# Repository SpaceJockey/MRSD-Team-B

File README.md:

MRSD-Team-B
===========

The best team is sometimes the B team...

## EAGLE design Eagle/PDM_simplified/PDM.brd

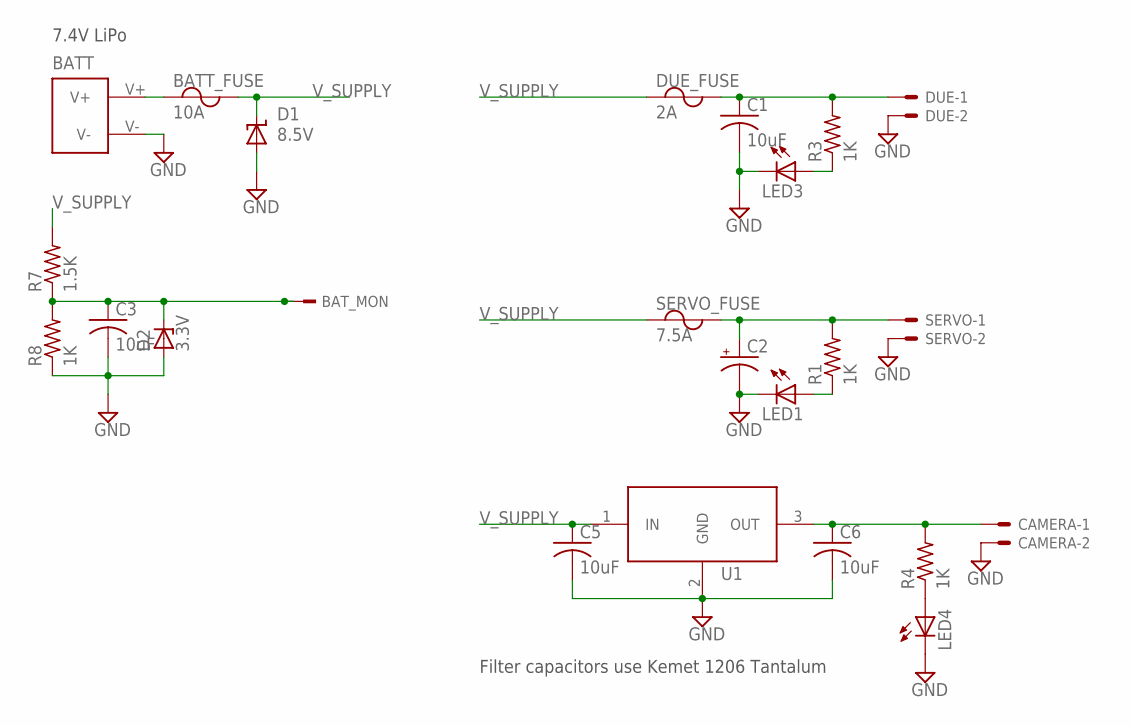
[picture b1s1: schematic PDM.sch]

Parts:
BATT: CON_XT60-; CON_XT60_PCB_MALE
BATT_FUSE: 10A; MINI_ATO
BAT_MON: TSW-101-02-S-S
C1, C3, C5, C6: 10uF; C1206K
C2: CPOL-USTT5D11; TT5D11
CAMERA: 5566-2
D1: 8.5V; SMBJ
D2: 3.3V; SOD80C
DUE: 5566-2
DUE_FUSE: 2A; MINI_ATO
LED1, LED3, LED4: LEDSML1206; SML1206
R1, R3, R4, R8: 1K; R1206
R7: 1.5K; R1206
SERVO: 5566-2
SERVO_FUSE: 7.5A; MINI_ATO
U1: MIC29150/29300/29500VERTICAL; TO220V

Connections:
GND: BATT.V-, C1.2, C2.-, C3.2, C5.2, C6.2, CAMERA.2, D1.A, D2.A, DUE.2, LED1.C, LED3.C, LED4.C, R8.1, SERVO.2, U1.2 (GND)
unnamed: BATT.V+, BATT_FUSE.P$2 (1)
unnamed: C1.1, DUE.1, DUE_FUSE.P$3 (2), R3.2
unnamed: LED1.A, R1.1
unnamed: C6.1, CAMERA.1, R4.2, U1.3 (OUT)
unnamed: LED3.A, R3.1
unnamed: LED4.A, R4.1
unnamed: C2.+, R1.2, SERVO.1, SERVO_FUSE.P$3 (2)
unnamed: BAT_MON.1, C3.1, D2.C, R7.1, R8.2
V_SUPPLY: BATT_FUSE.P$3 (2), C5.1, D1.C, DUE_FUSE.P$2 (1), R7.2, SERVO_FUSE.P$2 (1), U1.1 (IN)

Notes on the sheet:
Filter capacitors use Kemet 1206 Tantalum
7.4V LiPo

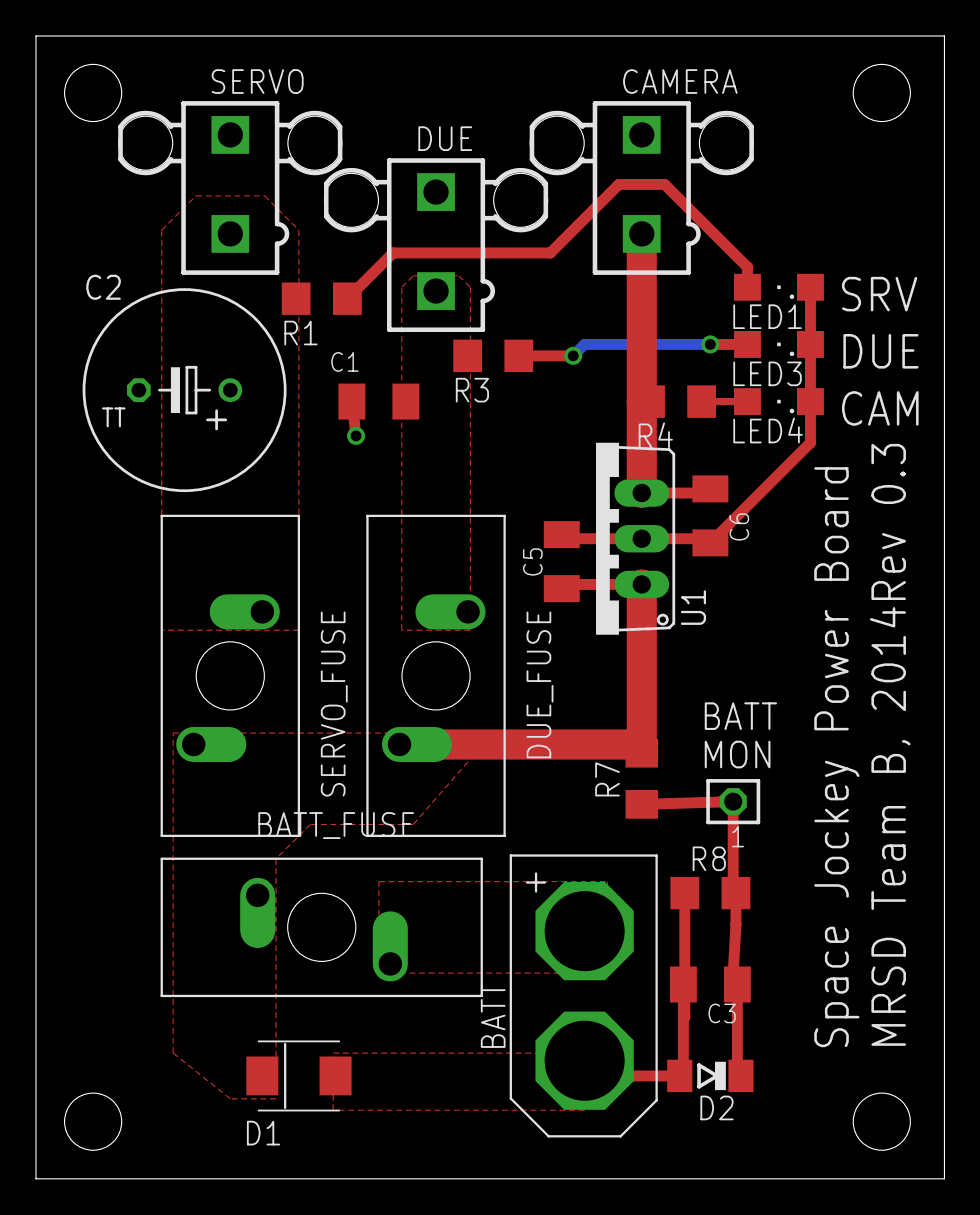
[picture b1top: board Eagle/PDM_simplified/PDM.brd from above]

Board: 2 copper layers, 50.5 x 63.5 mm, 24 parts (0 on the bottom side), 10 nets.

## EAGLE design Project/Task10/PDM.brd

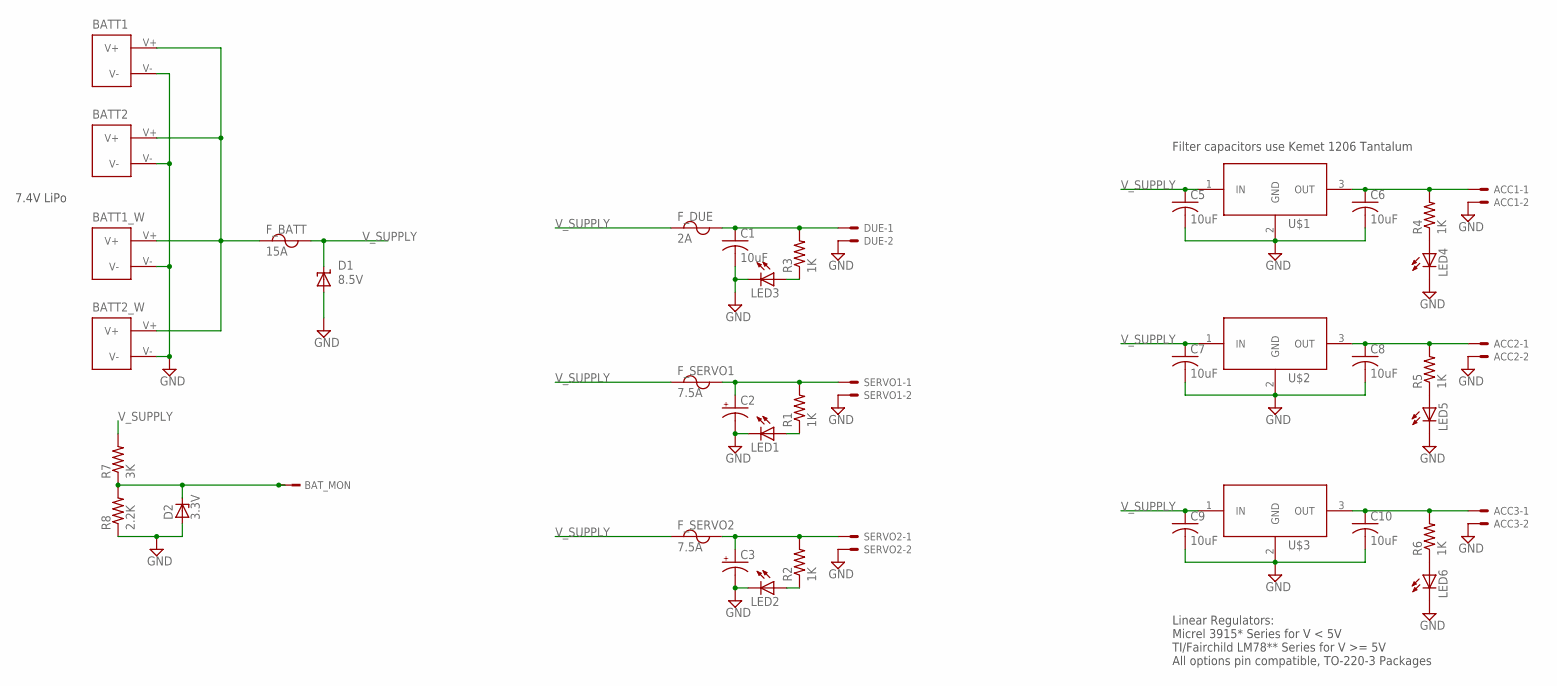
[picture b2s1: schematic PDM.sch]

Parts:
ACC1, ACC2, ACC3: 5566-2
BATT1, BATT2: CON_XT60-PCB_MOUNT; CON_XT60_PCB_MOUNT
BATT1_W, BATT2_W: CON_XT60-PIGTAIL; CON_XT60_PIGTAIL
BAT_MON: TSW-101-02-S-S
C1, C5, C6, C7, C8, C9, C10: 10uF; C1206K
C2, C3: CPOL-USTT5D11; TT5D11
D1: 8.5V; SMBJ
D2: 3.3V; SMB
DUE: 5566-2
F_BATT: 15A; ATO
F_DUE: 2A; ATO
F_SERVO1, F_SERVO2: 7.5A; ATO
LED1, LED2, LED3, LED4, LED5, LED6: LEDSML1206; SML1206
R1, R2, R3, R4, R5, R6: 1K; R1206
R7: 3K; R1206
R8: 2.2K; R1206
SERVO1, SERVO2: 5566-2
U$1, U$2, U$3: MIC29150/29300/29500VERTICAL; TO220V

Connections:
GND: ACC1.2, ACC2.2, ACC3.2, BATT1.V-, BATT1_W.V-, BATT2.V-, BATT2_W.V-, C1.2, C2.-, C3.-, C5.2, C6.2, C7.2, C8.2, C9.2, C10.2, D1.A, D2.A, DUE.2, LED1.C, LED2.C, LED3.C, LED4.C, LED5.C, LED6.C, R8.1, SERVO1.2, SERVO2.2, U$1.2 (GND), U$2.2 (GND), U$3.2 (GND)
unnamed: C3.+, F_SERVO2.B1 (2), F_SERVO2.B2 (2), F_SERVO2.B3 (2), F_SERVO2.B4 (2), R2.2, SERVO2.1
unnamed: BATT1.V+, BATT1_W.V+, BATT2.V+, BATT2_W.V+, F_BATT.A1 (1), F_BATT.A2 (1), F_BATT.A3 (1), F_BATT.A4 (1)
unnamed: C1.1, DUE.1, F_DUE.B1 (2), F_DUE.B2 (2), F_DUE.B3 (2), F_DUE.B4 (2), R3.2
unnamed: LED1.A, R1.1
unnamed: ACC1.1, C6.1, R4.2, U$1.3 (OUT)
unnamed: LED2.A, R2.1
unnamed: ACC2.1, C8.1, R5.2, U$2.3 (OUT)
unnamed: LED3.A, R3.1
unnamed: LED4.A, R4.1
unnamed: C2.+, F_SERVO1.B1 (2), F_SERVO1.B2 (2), F_SERVO1.B3 (2), F_SERVO1.B4 (2), R1.2, SERVO1.1
unnamed: LED5.A, R5.1
unnamed: BAT_MON.1, D2.C, R7.1, R8.2
unnamed: ACC3.1, C10.1, R6.2, U$3.3 (OUT)
unnamed: LED6.A, R6.1
V_SUPPLY: C5.1, C7.1, C9.1, D1.C, F_BATT.B1 (2), F_BATT.B2 (2), F_BATT.B3 (2), F_BATT.B4 (2), F_DUE.A1 (1), F_DUE.A2 (1), F_DUE.A3 (1), F_DUE.A4 (1), F_SERVO1.A1 (1), F_SERVO1.A2 (1), F_SERVO1.A3 (1), F_SERVO1.A4 (1), F_SERVO2.A1 (1), F_SERVO2.A2 (1), F_SERVO2.A3 (1), F_SERVO2.A4 (1), R7.2, U$1.1 (IN), U$2.1 (IN), U$3.1 (IN)

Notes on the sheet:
Linear Regulators: Micrel 3915* Series for V < 5V TI/Fairchild LM78** Series for V >= 5V All options pin compatible, TO-220-3 Packages
Filter capacitors use Kemet 1206 Tantalum
7.4V LiPo

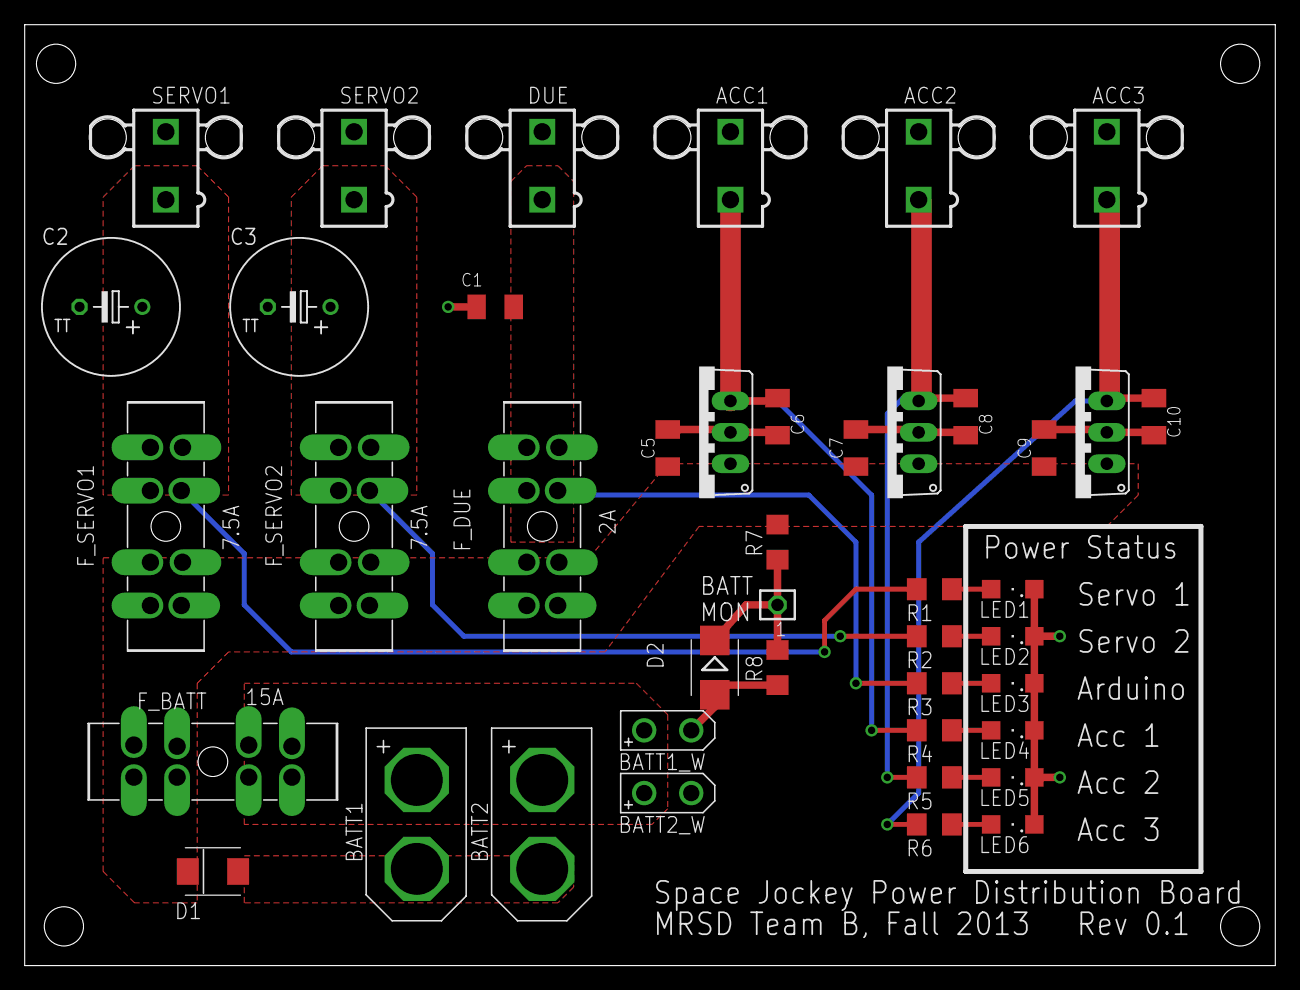
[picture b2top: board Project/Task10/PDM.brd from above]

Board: 2 copper layers, 101.3 x 76.2 mm, 43 parts (0 on the bottom side), 16 nets.

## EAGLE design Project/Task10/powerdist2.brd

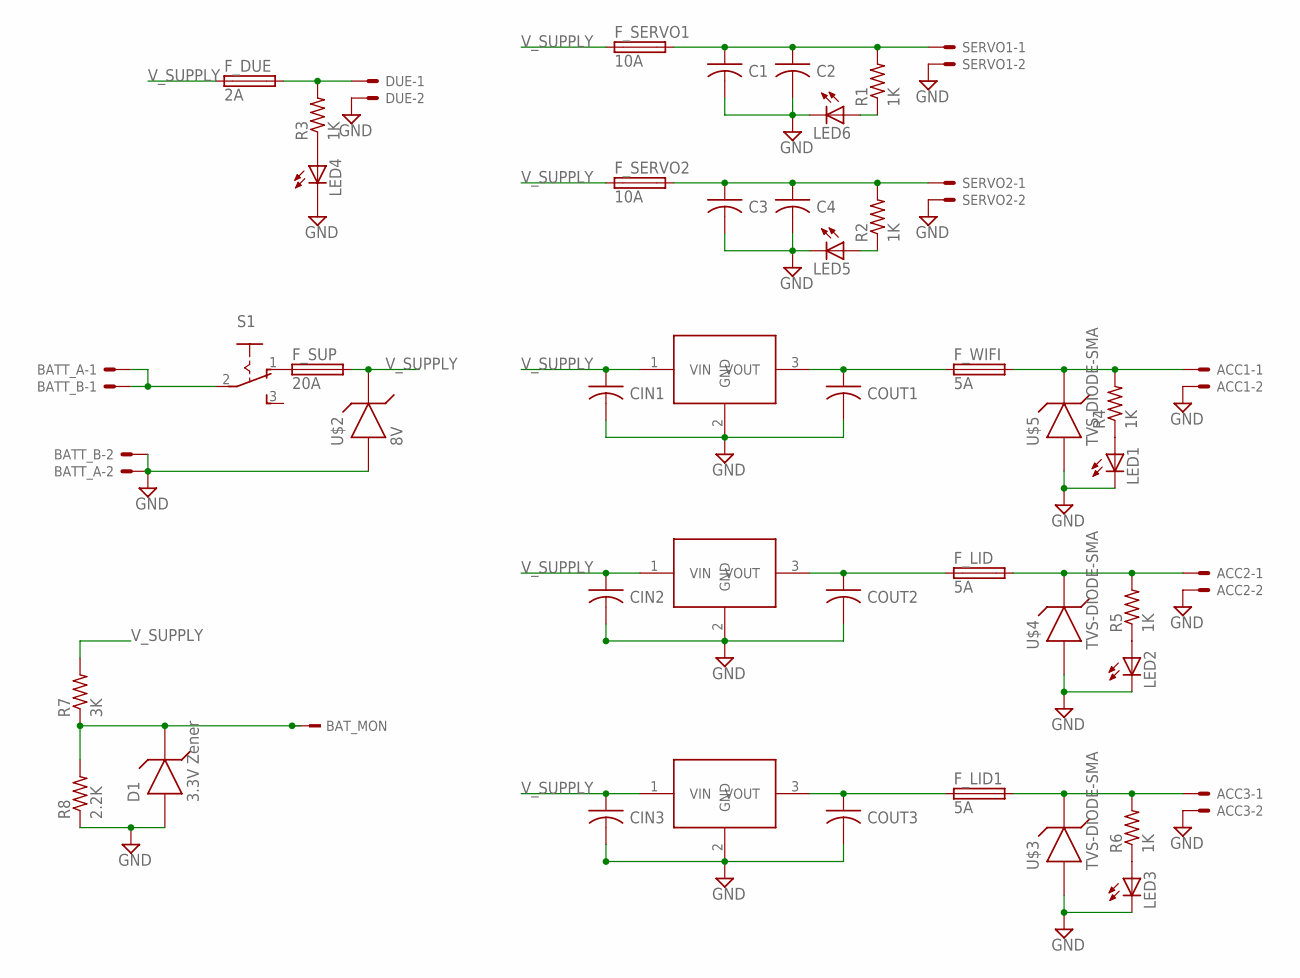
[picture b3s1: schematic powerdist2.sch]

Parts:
ACC1: C-GRID-02-70553; 70553-02
ACC2, ACC3: 5566-2
BATT_A: 22-23-2021
BATT_B: 22-23-2021
BAT_MON: TSW-101-02-S-S
C1, C2, C3, C4: CAPACITORTH_CAP; C025-025X050
CIN1, CIN2, CIN3: CAPACITORTH_CAP; C025-025X050
COUT1, COUT2, COUT3: CAPACITORTH_CAP; C025-025X050
D1: 3.3V Zener; SMA
DUE: C-GRID-02-70553; 70553-02
F_DUE: 2A; GSH15
F_LID, F_LID1: 5A; GSH15
F_SERVO1, F_SERVO2: 10A; GSH15
F_SUP: 20A; GSH15
F_WIFI: 5A; GSH15
LED1, LED2, LED3, LED4, LED5, LED6: LEDCHIP-LED0805; CHIP-LED0805
R1, R2, R3, R4, R5, R6: 1K; 0309/10
R7: 3K; 0309/10
R8: 2.2K; 0309/10
S1: 255SB
SERVO1, SERVO2: 5566-2
U$1, U$6, U$7: MIC29150/29300/29500; TO220
U$2: 8V; SMA
U$3, U$4, U$5: TVS-DIODE-SMA; SMA

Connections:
GND: ACC1.2, ACC2.2, ACC3.2, BATT_A.2, BATT_B.2, C1.2, C2.2, C3.2, C4.2, CIN1.2, CIN2.2, CIN3.2, COUT1.2, COUT2.2, COUT3.2, D1.AN, DUE.2, LED1.C, LED2.C, LED3.C, LED4.C, LED5.C, LED6.C, R8.1, SERVO1.2, SERVO2.2, U$1.2 (GND), U$2.AN, U$3.AN, U$4.AN, U$5.AN, U$6.2 (GND), U$7.2 (GND)
unnamed: C3.1, C4.1, F_SERVO2.2, R2.2, SERVO2.1
unnamed: ACC2.1, F_LID.2, R5.2, U$4.CAT
unnamed: DUE.1, F_DUE.2, R3.2
unnamed: LED6.A, R1.1
unnamed: COUT1.1, F_WIFI.1, U$7.3 (VOUT)
unnamed: ACC1.1, F_WIFI.2, R4.2, U$5.CAT
unnamed: LED5.A, R2.1
unnamed: COUT2.1, F_LID.1, U$6.3 (VOUT)
unnamed: BATT_A.1, BATT_B.1, S1.2
unnamed: LED4.A, R3.1
unnamed: LED1.A, R4.1
unnamed: F_SUP.1, S1.1 (O)
unnamed: C1.1, C2.1, F_SERVO1.2, R1.2, SERVO1.1
unnamed: LED2.A, R5.1
unnamed: BAT_MON.1, D1.CAT, R7.1, R8.2
unnamed: COUT3.1, F_LID1.1, U$1.3 (VOUT)
unnamed: ACC3.1, F_LID1.2, R6.2, U$3.CAT
unnamed: LED3.A, R6.1
V_SUPPLY: CIN1.1, CIN2.1, CIN3.1, F_DUE.1, F_SERVO1.1, F_SERVO2.1, F_SUP.2, R7.2, U$1.1 (VIN), U$2.CAT, U$6.1 (VIN), U$7.1 (VIN)

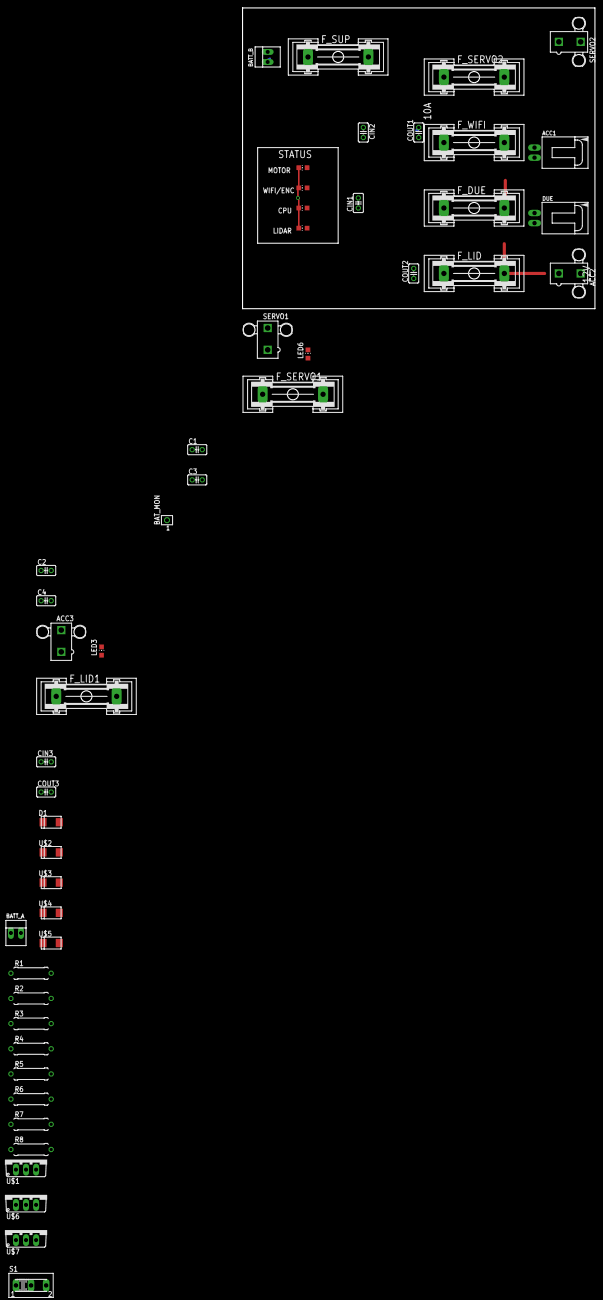
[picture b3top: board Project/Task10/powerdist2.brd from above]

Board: 2 copper layers, 88.9 x 75.9 mm, 49 parts (0 on the bottom side), 20 nets.

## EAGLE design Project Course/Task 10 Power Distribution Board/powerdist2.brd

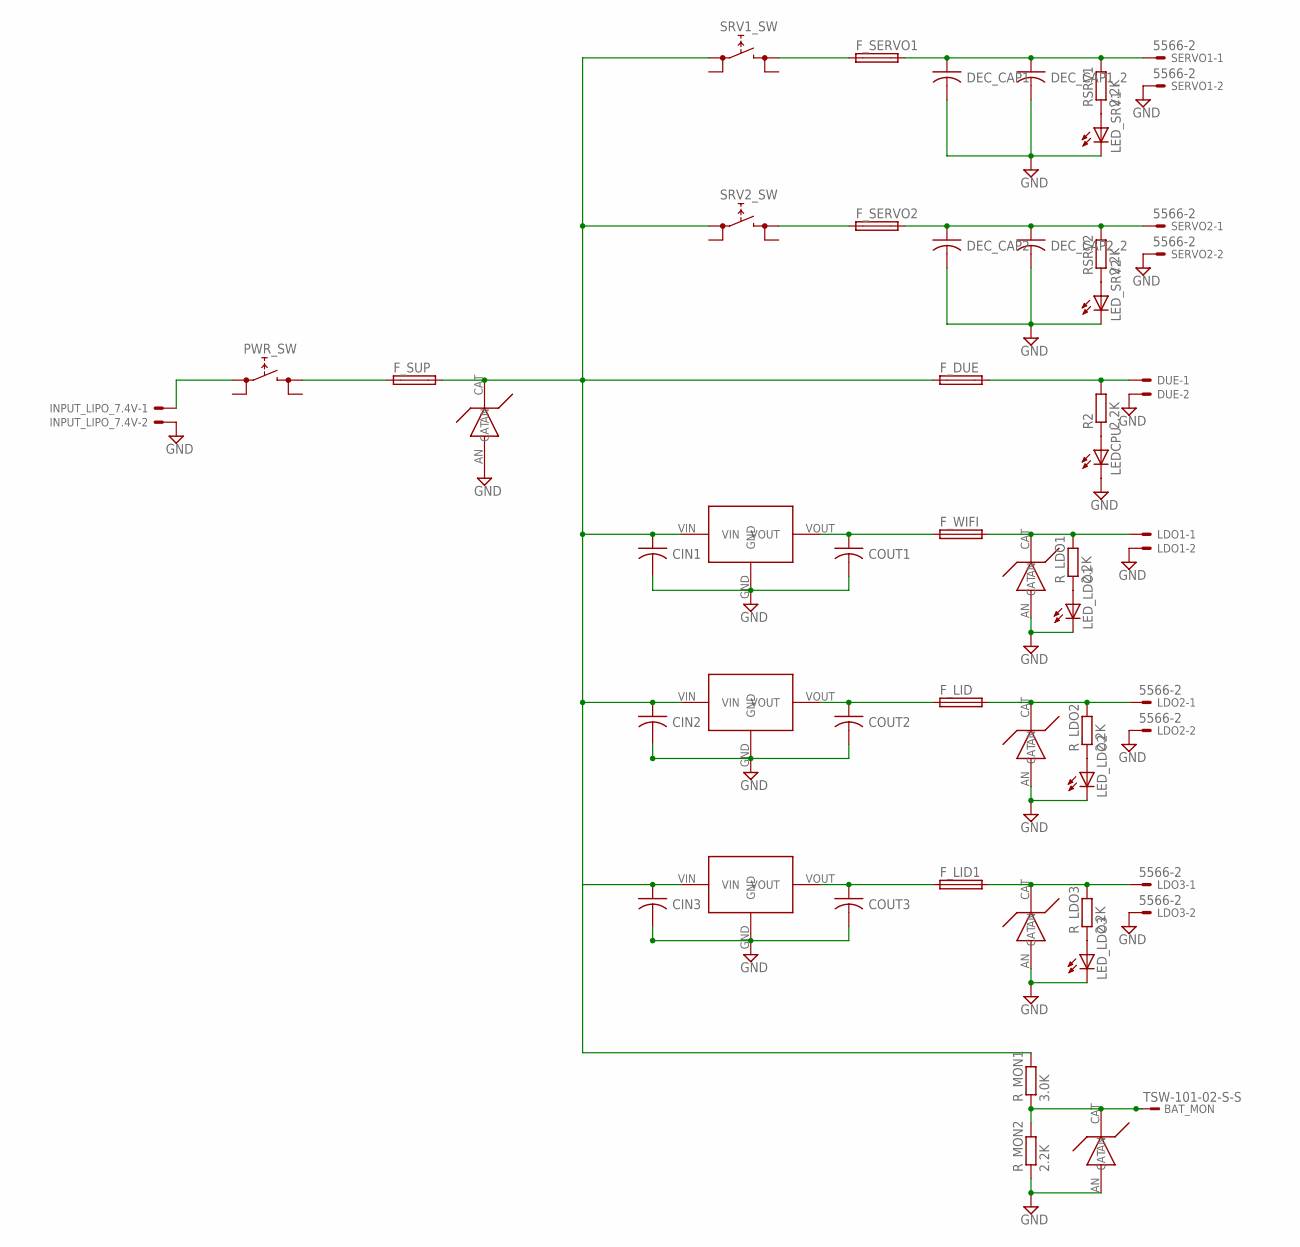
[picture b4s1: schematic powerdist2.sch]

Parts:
BAT_MON: TSW-101-02-S-S
CIN1, CIN2, CIN3: CAPACITORTH_CAP; C025-025X050
COUT1, COUT2, COUT3: CAPACITORTH_CAP; C025-025X050
DEC_CAP1, DEC_CAP1_2, DEC_CAP2, DEC_CAP2_2: CAPACITORTH_CAP; C025-025X050
DUE: C-GRID-02-70553; 70553-02
F_DUE: GSH15
F_LID, F_LID1: GSH15
F_SERVO1, F_SERVO2: GSH15
F_SUP: GSH15
F_WIFI: GSH15
INPUT_LIPO_7.4V: 22-23-2021
LDO1: C-GRID-02-70553; 70553-02
LDO2, LDO3: 5566-2
LEDCPU: LEDCHIP-LED0805; CHIP-LED0805
LED_LDO1, LED_LDO2, LED_LDO3: LEDCHIP-LED0805; CHIP-LED0805
LED_SRV1, LED_SRV2: LEDCHIP-LED0805; CHIP-LED0805
LID12V1A, LID12V1A1: MIC29150/29300/29500
PWR_SW: REKN
R2: 2.2K; R0402
RSRV1, RSRV2: 2.2K; R0402
R_LDO1, R_LDO2, R_LDO3: 2.2K; R0402
R_MON1: 3.0K; R0402
R_MON2: 2.2K; R0402
SERVO1, SERVO2: 5566-2
SRV1_SW, SRV2_SW: REKN
TVS-MAIN: 26V; TVS-SMAJ
TVS-MAIN1, TVS-MAIN3: 16V; TVS-SMAJ
TVS-MAIN2: 5V; TVS-SMAJ
TVS_3.3: 16V; TVS-SMAJ
WIFI5V1A1: MIC29150/29300/29500

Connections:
GND: CIN1.2, CIN2.2, CIN3.2, COUT1.2, COUT2.2, COUT3.2, DEC_CAP1.2, DEC_CAP1_2.2, DEC_CAP2.2, DEC_CAP2_2.2, DUE.2, INPUT_LIPO_7.4V.2, LDO1.2, LDO2.2, LDO3.2, LEDCPU.C, LED_LDO1.C, LED_LDO2.C, LED_LDO3.C, LED_SRV1.C, LED_SRV2.C, LID12V1A.GND, LID12V1A1.GND, R_MON2.1, SERVO1.2, SERVO2.2, TVS-MAIN.AN, TVS-MAIN1.AN, TVS-MAIN2.AN, TVS-MAIN3.AN, TVS_3.3.AN, WIFI5V1A1.GND
unnamed: DEC_CAP2.1, DEC_CAP2_2.1, F_SERVO2.2, RSRV2.2, SERVO2.1
unnamed: F_LID.2, LDO2.1, R_LDO2.2, TVS-MAIN3.CAT
unnamed: F_SERVO1.1, SRV1_SW.1A (1)
unnamed: DUE.1, F_DUE.2, R2.2
unnamed: LED_SRV2.A, RSRV2.1
unnamed: COUT1.1, F_WIFI.1, WIFI5V1A1.VOUT
unnamed: F_WIFI.2, LDO1.1, R_LDO1.2, TVS-MAIN2.CAT
unnamed: LEDCPU.A, R2.1
unnamed: COUT2.1, F_LID.1, LID12V1A.VOUT
unnamed: INPUT_LIPO_7.4V.1, PWR_SW.0A (0)
unnamed: LED_LDO1.A, R_LDO1.1
unnamed: CIN1.1, CIN2.1, F_DUE.1, F_SUP.2, LID12V1A.VIN, R_MON1.2, SRV1_SW.0A (0), SRV2_SW.0A (0), TVS-MAIN.CAT, WIFI5V1A1.VIN
unnamed: LED_LDO2.A, R_LDO2.1
unnamed: F_SUP.1, PWR_SW.1A (1)
unnamed: DEC_CAP1.1, DEC_CAP1_2.1, F_SERVO1.2, RSRV1.2, SERVO1.1
unnamed: LED_SRV1.A, RSRV1.1
unnamed: F_SERVO2.1, SRV2_SW.1A (1)
unnamed: BAT_MON.1, R_MON1.1, R_MON2.2, TVS_3.3.CAT
unnamed: COUT3.1, F_LID1.1, LID12V1A1.VOUT
unnamed: CIN3.1, LID12V1A1.VIN
unnamed: F_LID1.2, LDO3.1, R_LDO3.2, TVS-MAIN1.CAT
unnamed: LED_LDO3.A, R_LDO3.1

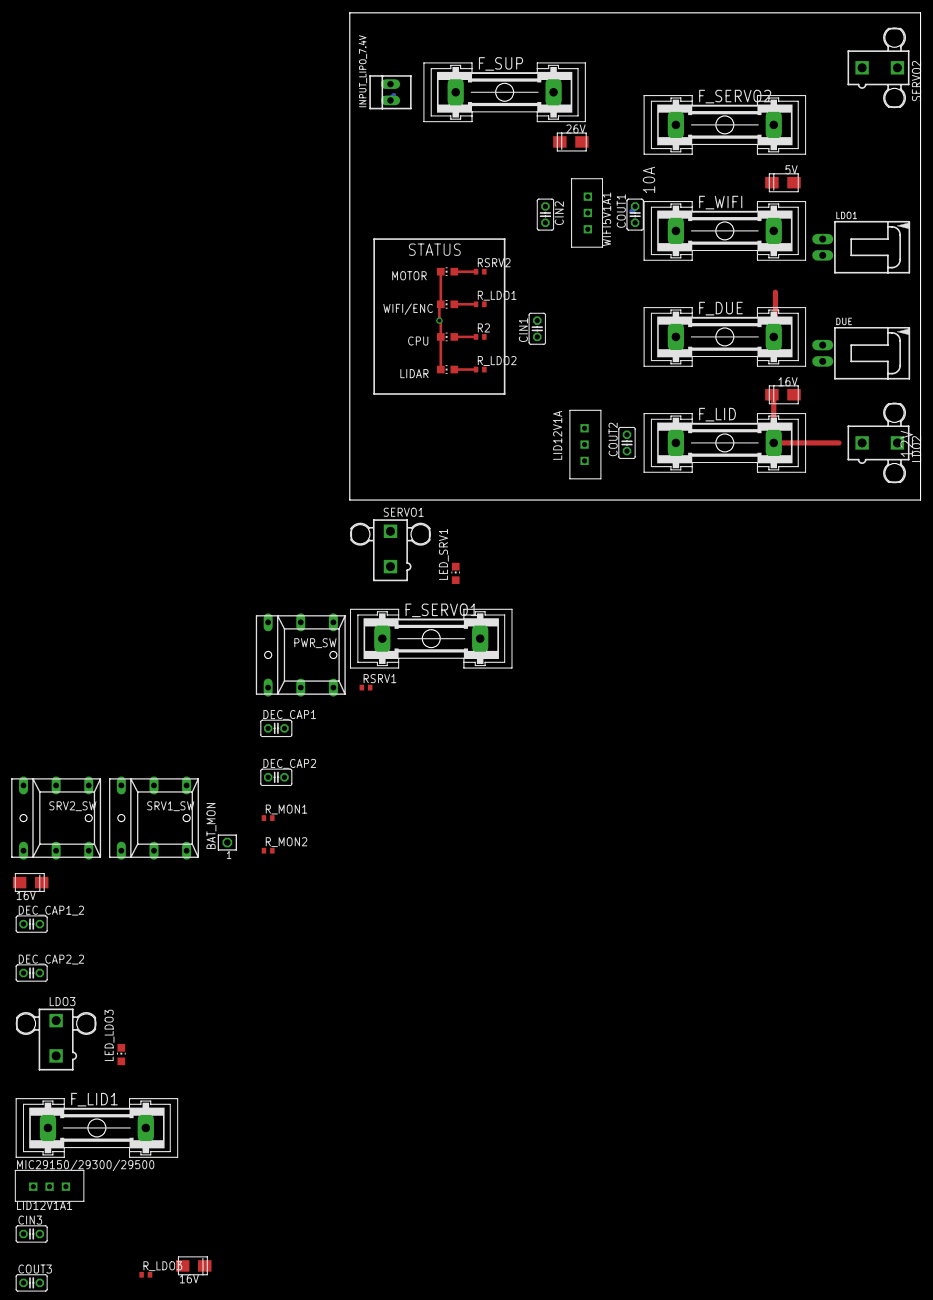
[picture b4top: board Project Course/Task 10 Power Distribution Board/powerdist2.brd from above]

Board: 2 copper layers, 88.9 x 75.9 mm, 50 parts (0 on the bottom side), 23 nets.

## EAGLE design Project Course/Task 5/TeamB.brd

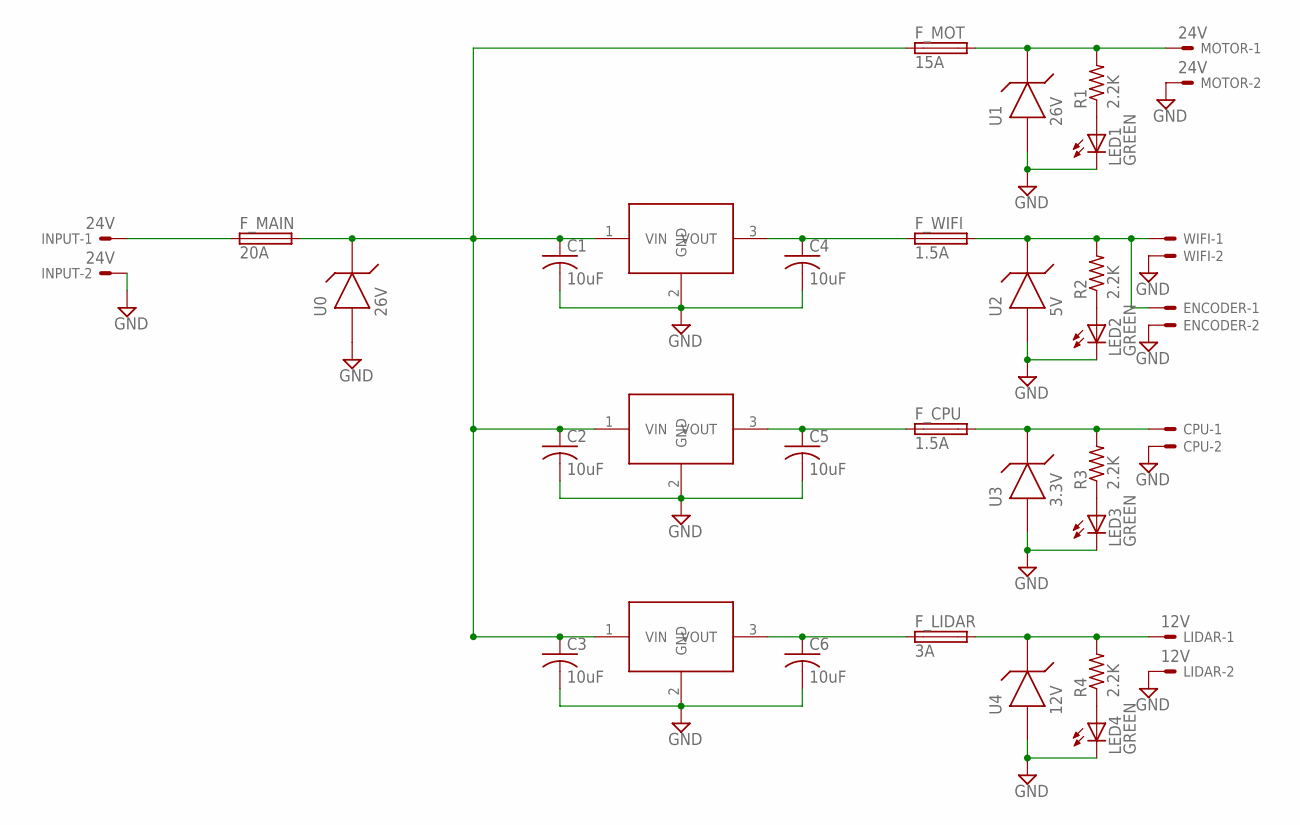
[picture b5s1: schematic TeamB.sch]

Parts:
C1, C2, C3, C4, C5, C6: 10uF; C1206
CPU: 3.3V; 70553-02
ENCODER: 5V; 70553-02
F_CPU: 1.5A; TE5
F_LIDAR: 3A; TE5
F_MAIN: 20A; TE5
F_MOT: 15A; TE5
F_WIFI: 1.5A; TE5
INPUT: 24V; 5566-2
LED1, LED2, LED3, LED4: GREEN; SML1206
LIDAR: 12V; 5566-2
MOTOR: 24V; 5566-2
Q1: MIC29300-5.0WU; TO220
Q2: MIC29300-3.3WU; TO220
Q3: MIC29300-12WU; TO220
R1, R2, R3, R4: 2.2K; R1206
U0, U1: 26V; SMA
U2: 5V; SMA
U3: 3.3V; SMB
U4: 12V; SMA
WIFI: 5V; 70553-02

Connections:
GND: C1.2, C2.2, C3.2, C4.2, C5.2, C6.2, CPU.2, ENCODER.2, INPUT.2, LED1.C, LED2.C, LED3.C, LED4.C, LIDAR.2, MOTOR.2, Q1.2 (GND), Q2.2 (GND), Q3.2 (GND), U0.AN, U1.AN, U2.AN, U3.AN, U4.AN, WIFI.2
unnamed: F_MOT.2, MOTOR.1, R1.2, U1.CAT
unnamed: F_LIDAR.2, LIDAR.1, R4.2, U4.CAT
unnamed: C5.1, F_CPU.1, Q2.3 (VOUT)
unnamed: CPU.1, F_CPU.2, R3.2, U3.CAT
unnamed: LED1.A, R1.1
unnamed: C4.1, F_WIFI.1, Q1.3 (VOUT)
unnamed: ENCODER.1, F_WIFI.2, R2.2, U2.CAT, WIFI.1
unnamed: LED2.A, R2.1
unnamed: C6.1, F_LIDAR.1, Q3.3 (VOUT)
unnamed: F_MAIN.1, INPUT.1
unnamed: LED3.A, R3.1
unnamed: C1.1, C2.1, C3.1, F_MAIN.2, F_MOT.1, Q1.1 (VIN), Q2.1 (VIN), Q3.1 (VIN), U0.CAT
unnamed: LED4.A, R4.1

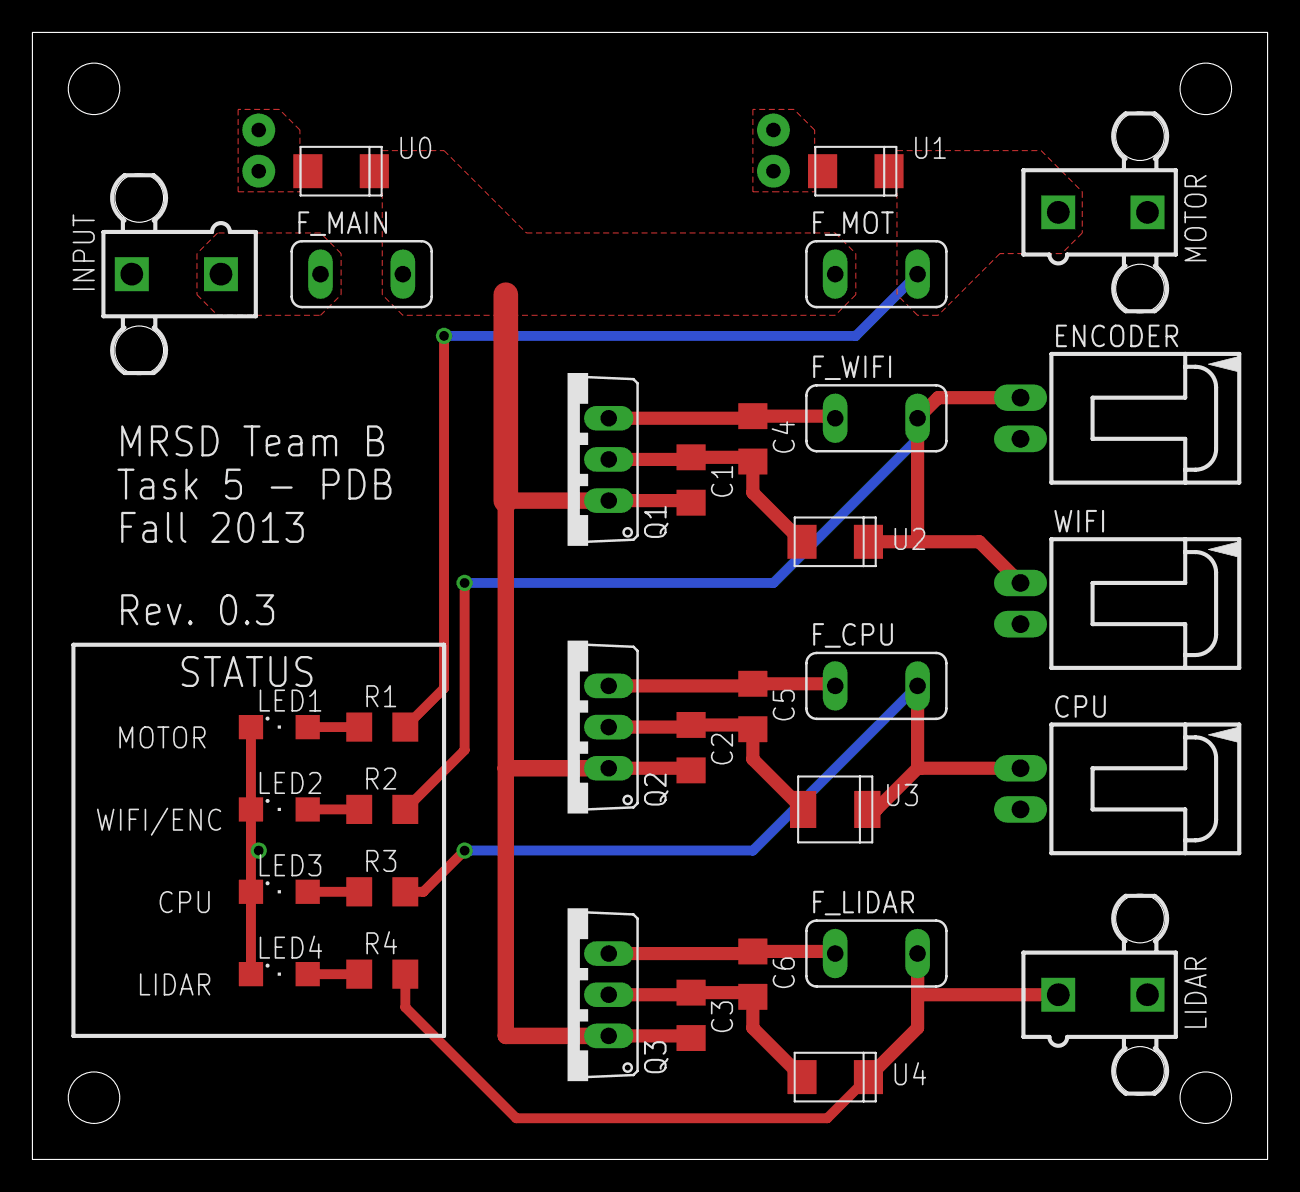
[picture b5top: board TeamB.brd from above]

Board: 2 copper layers, 76.2 x 69.5 mm, 33 parts (0 on the bottom side), 14 nets.

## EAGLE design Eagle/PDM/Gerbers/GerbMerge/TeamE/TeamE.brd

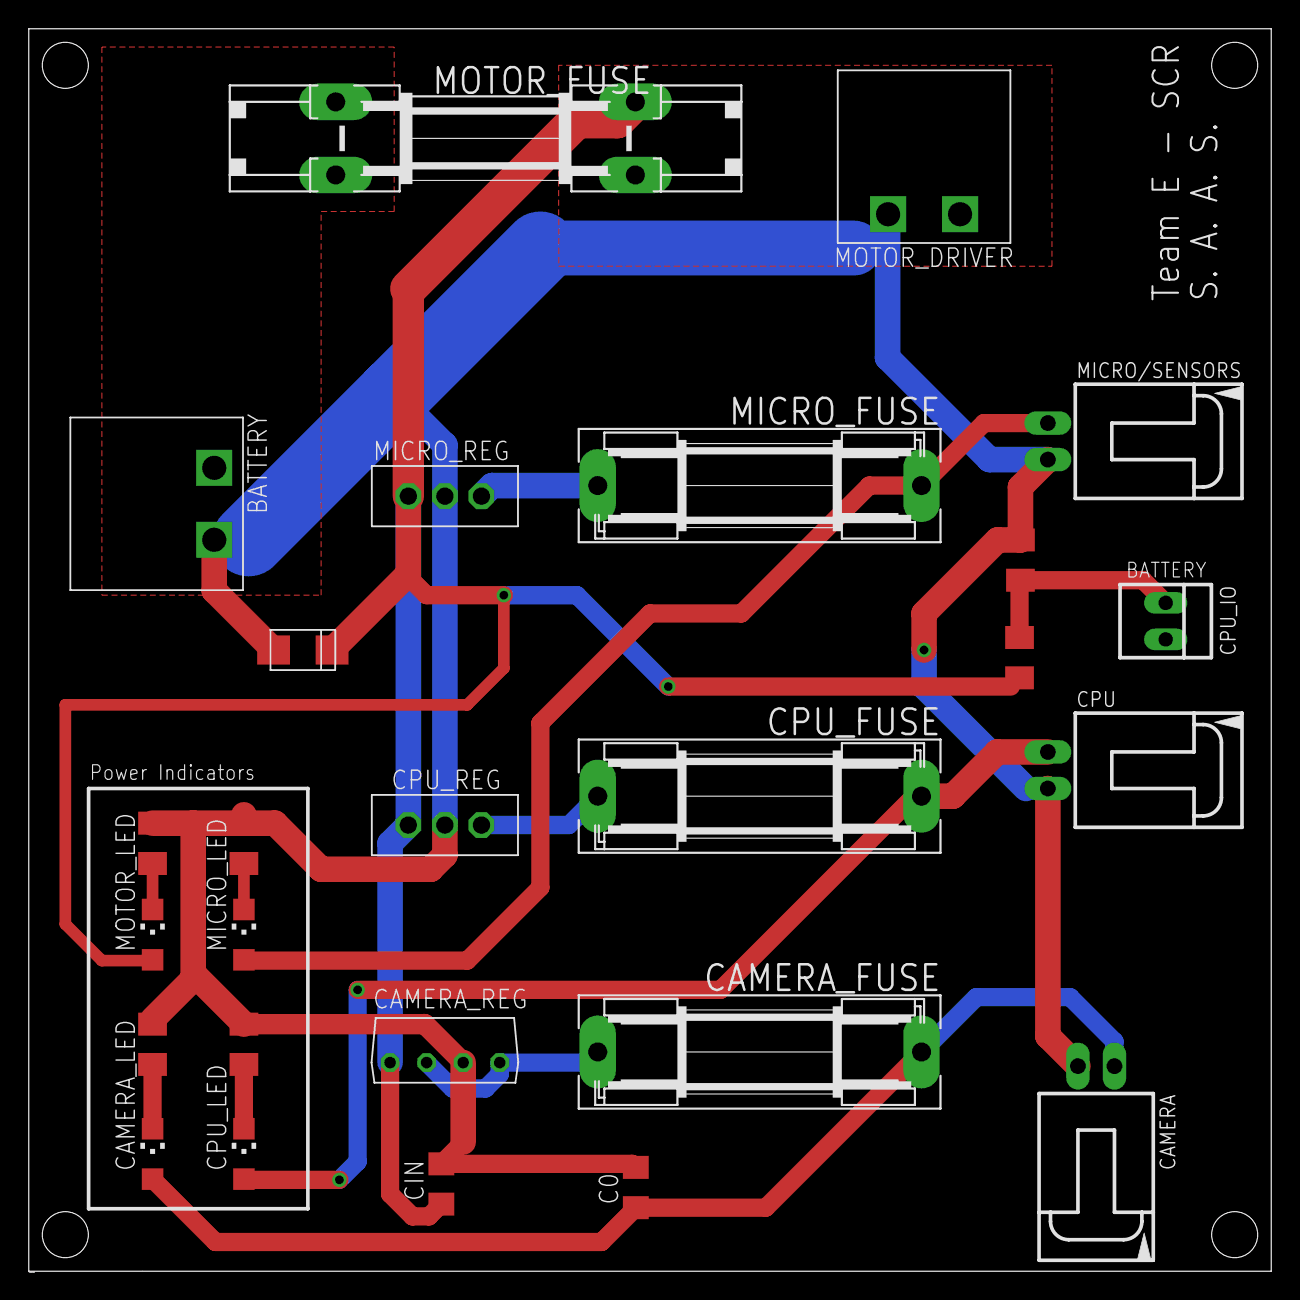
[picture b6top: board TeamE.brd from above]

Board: 2 copper layers, 86.4 x 86.4 mm, 26 parts (0 on the bottom side), 14 nets.

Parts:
BATTERY: TERMINAL-BLOCK; TERM-BLOCK
C0: 47 uF; C1206
CAMERA: C-GRID-02-70553; 70553-02
CAMERA_FUSE: 2.5A; SH22,5
CAMERA_LED: GREEN; CHIPLED_1206
CAMERA_REG: 12V-REGULATOR-2A; PQ05RD21
CIN: 33 uF; C1206
CPU: C-GRID-02-70553; 70553-02
CPU_FUSE: 1.5A; SH22,5
CPU_IO: 22-23-2021
CPU_LED: YELLOW; CHIPLED_1206
CPU_REG: 5V-REGULATOR-1.5A; TO-220
MICRO/SENSORS: C-GRID-02-70553; 70553-02
MICRO_FUSE: 1.5A; SH22,5
MICRO_LED: RED; CHIPLED_1206
MICRO_REG: 8V-REGULATOR-1.5A; TO-220
MOTOR_DRIVER: TERMINAL-BLOCK; TERM-BLOCK
MOTOR_FUSE: 16A; SHKOG
MOTOR_LED: BLUE; CHIPLED_1206
R1: 1k; M1206
R2, R3: 500; M1206
R4, R6: 2k; M1206
R5: 4.2k; M1206
SYS_DIODE: 17V-TVS-B; SMA

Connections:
GND: BATTERY.MINUS, C0.2, CAMERA.2, CAMERA_REG.GND, CIN.2, CPU.2, CPU_REG.GND, MICRO/SENSORS.2, MICRO_REG.GND, MOTOR_DRIVER.MINUS, R1.2, R2.2, R3.2, R4.1, R6.2, SYS_DIODE.CATHODE
unnamed: CPU_IO.1, R5.2, R6.1
unnamed: CAMERA_LED.C, R1.1
unnamed: MICRO_LED.C, R2.1
unnamed: CPU_LED.C, R3.1
unnamed: MOTOR_LED.C, R4.2
unnamed: CPU_FUSE.2, CPU_REG.OUTPUT
unnamed: CPU.1, CPU_FUSE.1, CPU_LED.A
unnamed: MICRO_FUSE.2, MICRO_REG.OUTPUT
unnamed: MICRO/SENSORS.1, MICRO_FUSE.1, MICRO_LED.A
unnamed: C0.1, CAMERA.1, CAMERA_FUSE.1, CAMERA_LED.A
unnamed: CAMERA_FUSE.2, CAMERA_REG.ON/OFF, CAMERA_REG.VOUT
VBATT: BATTERY.PLUS, MOTOR_FUSE.1A
VCC: CAMERA_REG.VIN, CIN.1, CPU_REG.INPUT, MICRO_REG.INPUT, MOTOR_DRIVER.PLUS, MOTOR_FUSE.2A, MOTOR_LED.A, R5.1, SYS_DIODE.ANNODE

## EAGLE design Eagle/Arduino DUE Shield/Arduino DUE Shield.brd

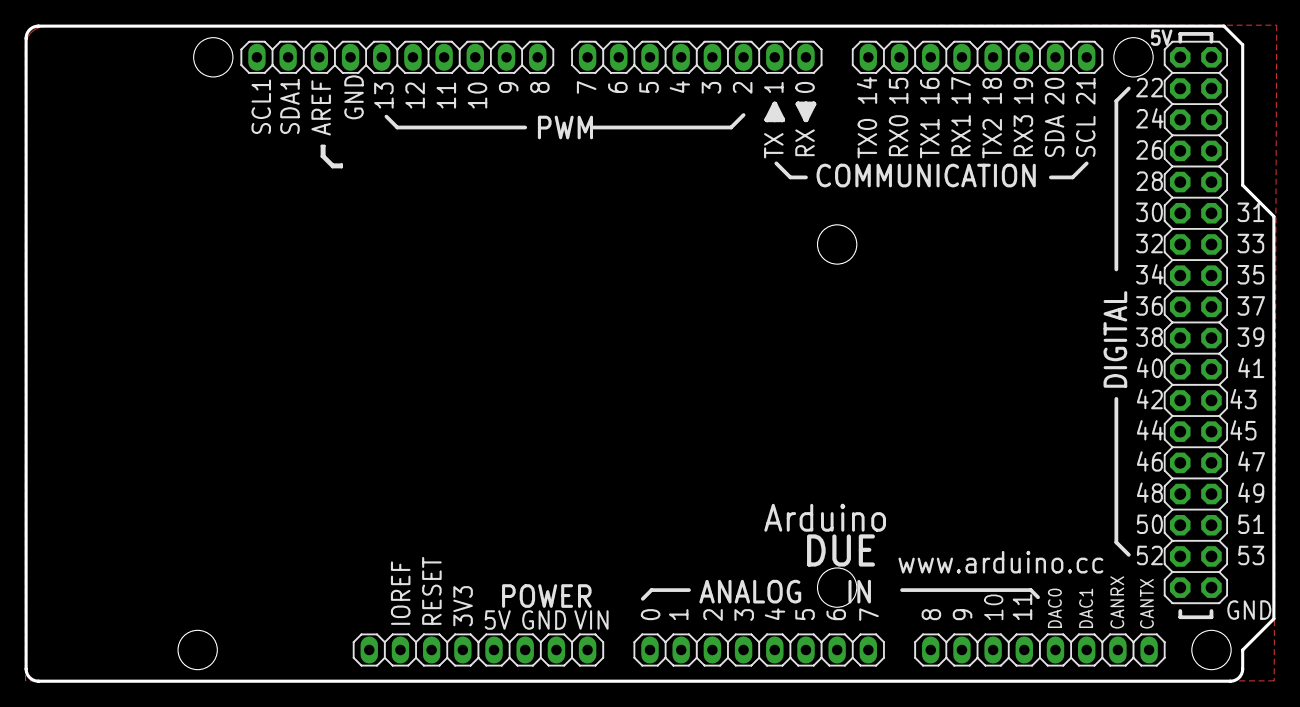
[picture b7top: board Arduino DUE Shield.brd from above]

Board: 4 copper layers, 101.6 x 53.3 mm, 7 parts (0 on the bottom side), 3 nets.

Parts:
ADCH: 8x1F-H8.5; 1X08
ADCL: 8x1F-H8.5; 1X08
COMMUNICATION: 8x1F-H8.5; 1X08
POWER: 8x1F-H8.5; 1X08
PWMH: 10x1F-H8.5; 1X10
PWML: 8x1F-H8.5; 1X08
XIO: 18x2F-H8.5; 2X18

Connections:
+3V3: POWER.2, POWER.4
+5V: POWER.5, XIO.1, XIO.2
GND: POWER.6, POWER.7, PWMH.7, XIO.35, XIO.36
